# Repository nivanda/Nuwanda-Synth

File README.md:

# Nuwanda-Synth
## Chord VCO:
Original Author: HAGIWO  
Link: https://www.youtube.com/watch?v=HeWXebKo_Yk&list=PLY98KKRLWqR2VkyIqR4JTxg3VBtVM9B-y&index=44  
## Mono/Sub VCO
Original Author: HAGIWO  
Link: https://www.youtube.com/watch?v=HBtc5oQffu8&list=PLY98KKRLWqR2VkyIqR4JTxg3VBtVM9B-y&index=40

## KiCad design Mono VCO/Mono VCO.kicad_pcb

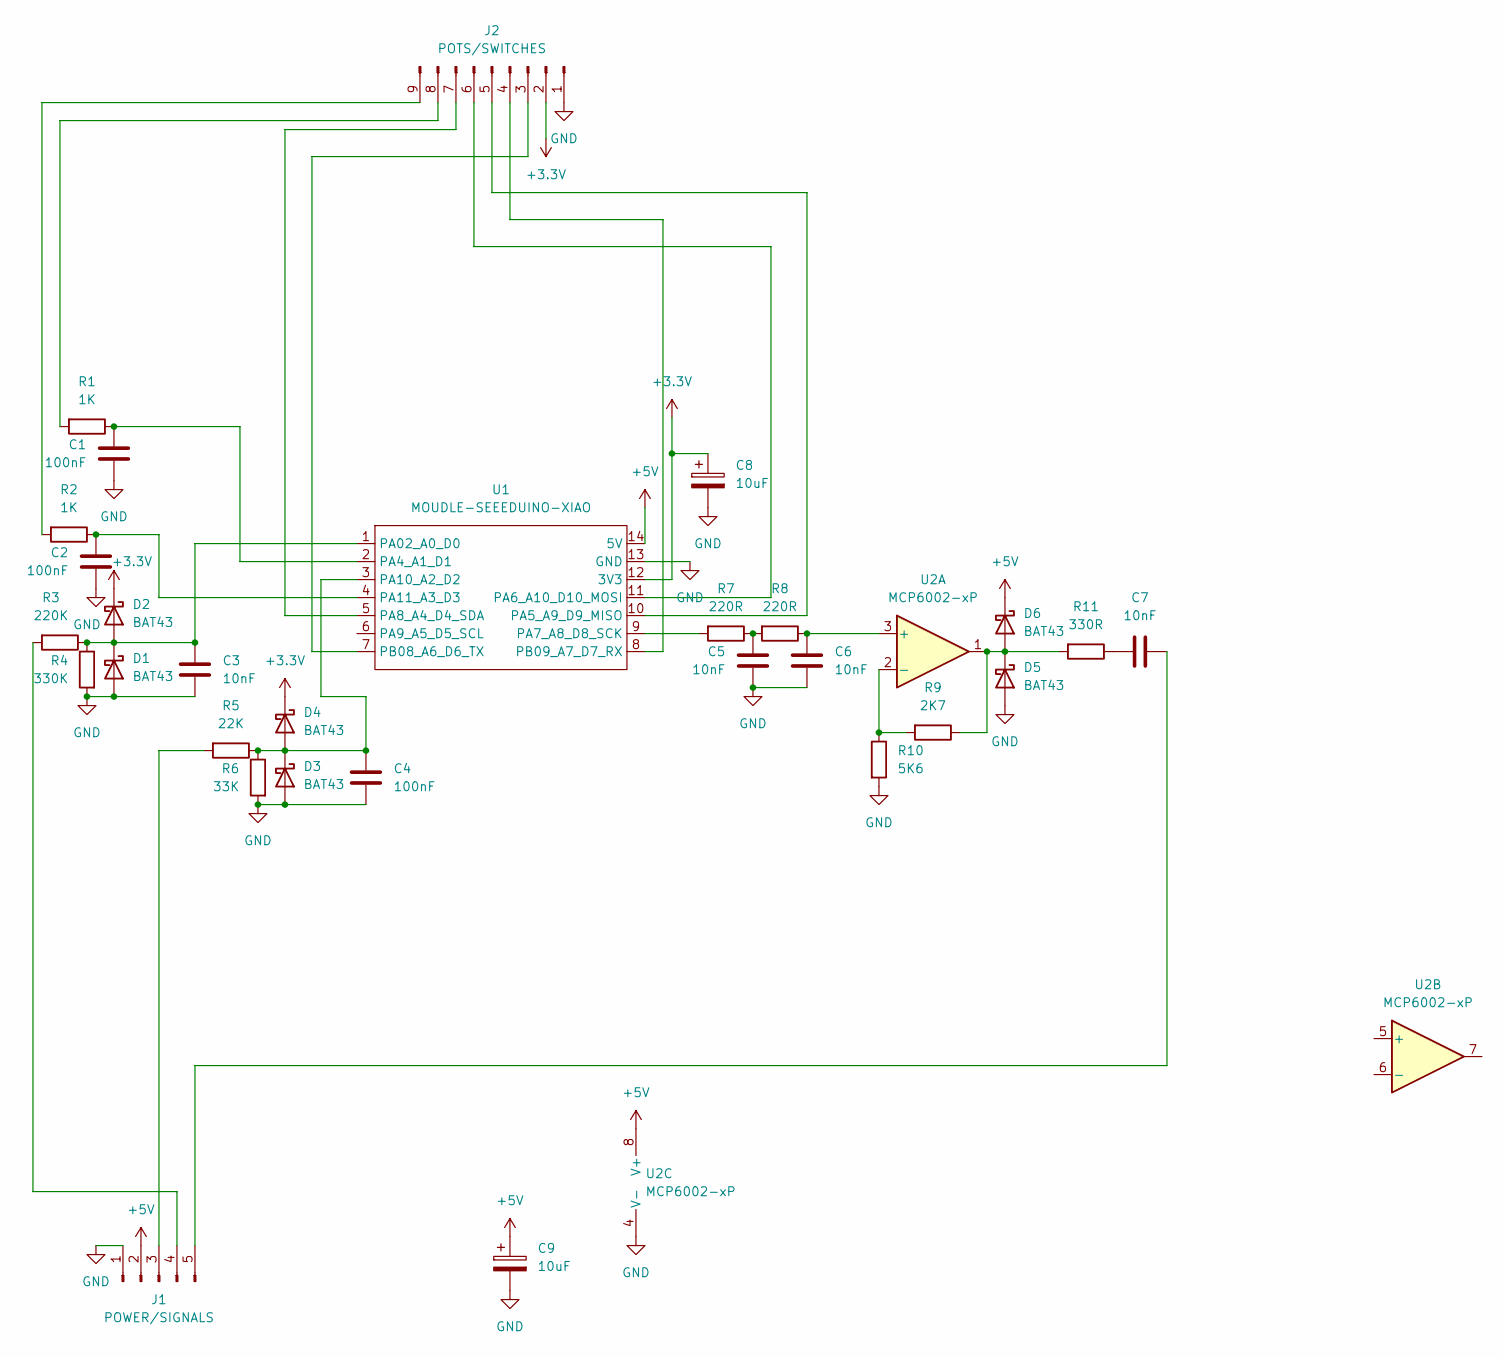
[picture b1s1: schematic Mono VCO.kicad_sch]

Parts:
C1, C2, C4: 100nF; C_Disc_D5.0mm_W2.5mm_P5.00mm
C3, C5, C6, C7: 10nF; C_Disc_D5.0mm_W2.5mm_P5.00mm
C8, C9: 10uF; CP_Radial_D5.0mm_P2.50mm
D1, D2, D3, D4, D5, D6: BAT43; D_DO-35_SOD27_P7.62mm_Horizontal
J1: POWER/SIGNALS; PinHeader_1x05_P2.54mm_Horizontal
J2: POTS/SWITCHES; PinHeader_1x09_P2.54mm_Horizontal
R1, R2: 1K; R_Axial_DIN0207_L6.3mm_D2.5mm_P10.16mm_Horizontal
R3: 220K; R_Axial_DIN0207_L6.3mm_D2.5mm_P10.16mm_Horizontal
R4: 330K; R_Axial_DIN0207_L6.3mm_D2.5mm_P10.16mm_Horizontal
R5: 22K; R_Axial_DIN0207_L6.3mm_D2.5mm_P10.16mm_Horizontal
R6: 33K; R_Axial_DIN0207_L6.3mm_D2.5mm_P10.16mm_Horizontal
R7, R8: 220R; R_Axial_DIN0207_L6.3mm_D2.5mm_P10.16mm_Horizontal
R9: 2K7; R_Axial_DIN0207_L6.3mm_D2.5mm_P10.16mm_Horizontal
R10: 5K6; R_Axial_DIN0207_L6.3mm_D2.5mm_P10.16mm_Horizontal
R11: 330R; R_Axial_DIN0207_L6.3mm_D2.5mm_P10.16mm_Horizontal
U1: MOUDLE-SEEEDUINO-XIAO; MOUDLE14P-2.54-21X17.8MM
U2: MCP6002-xP; DIP-8_W7.62mm_Socket

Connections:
+3.3V: C8.1, D2.1 (K), D4.1 (K), J2.2, U1.12 (3V3)
+5V: C9.1, D6.1 (K), J1.2, U1.14 (5V), U2.8 (V+)
GND: C1.2, C2.2, C3.2, C4.2, C5.2, C6.2, C8.2, C9.2, D1.2 (A), D3.2 (A), D5.2 (A), J1.1, J2.1, R4.2, R6.2, R10.2, U1.13 (GND), U2.4 (V-)
unnamed: C5.1, R7.1, R8.2
unnamed: C7.2, R11.1
unnamed: C3.1, D1.1 (K), D2.2 (A), R3.1, R4.1, U1.1 (PA02_A0_D0)
unnamed: C4.1, D3.1 (K), D4.2 (A), R5.1, R6.1, U1.3 (PA10_A2_D2)
unnamed: D5.1 (K), D6.2 (A), R9.1, R11.2, U2.1
unnamed: J1.3, R5.2
unnamed: J1.4, R3.2
unnamed: C7.1, J1.5
unnamed: J2.3, U1.7 (PB08_A6_D6_TX)
unnamed: J2.4, U1.8 (PB09_A7_D7_RX)
unnamed: J2.5, U1.10 (PA5_A9_D9_MISO)
unnamed: J2.6, U1.11 (PA6_A10_D10_MOSI)
unnamed: J2.7, U1.5 (PA8_A4_D4_SDA)
unnamed: J2.8, R1.2
unnamed: J2.9, R2.2
unnamed: C1.1, R1.1, U1.2 (PA4_A1_D1)
unnamed: R7.2, U1.9 (PA7_A8_D8_SCK)
unnamed: C2.1, R2.1, U1.4 (PA11_A3_D3)
unnamed: C6.1, R8.1, U2.3 (+)
unnamed: R9.2, R10.1, U2.2 (-)

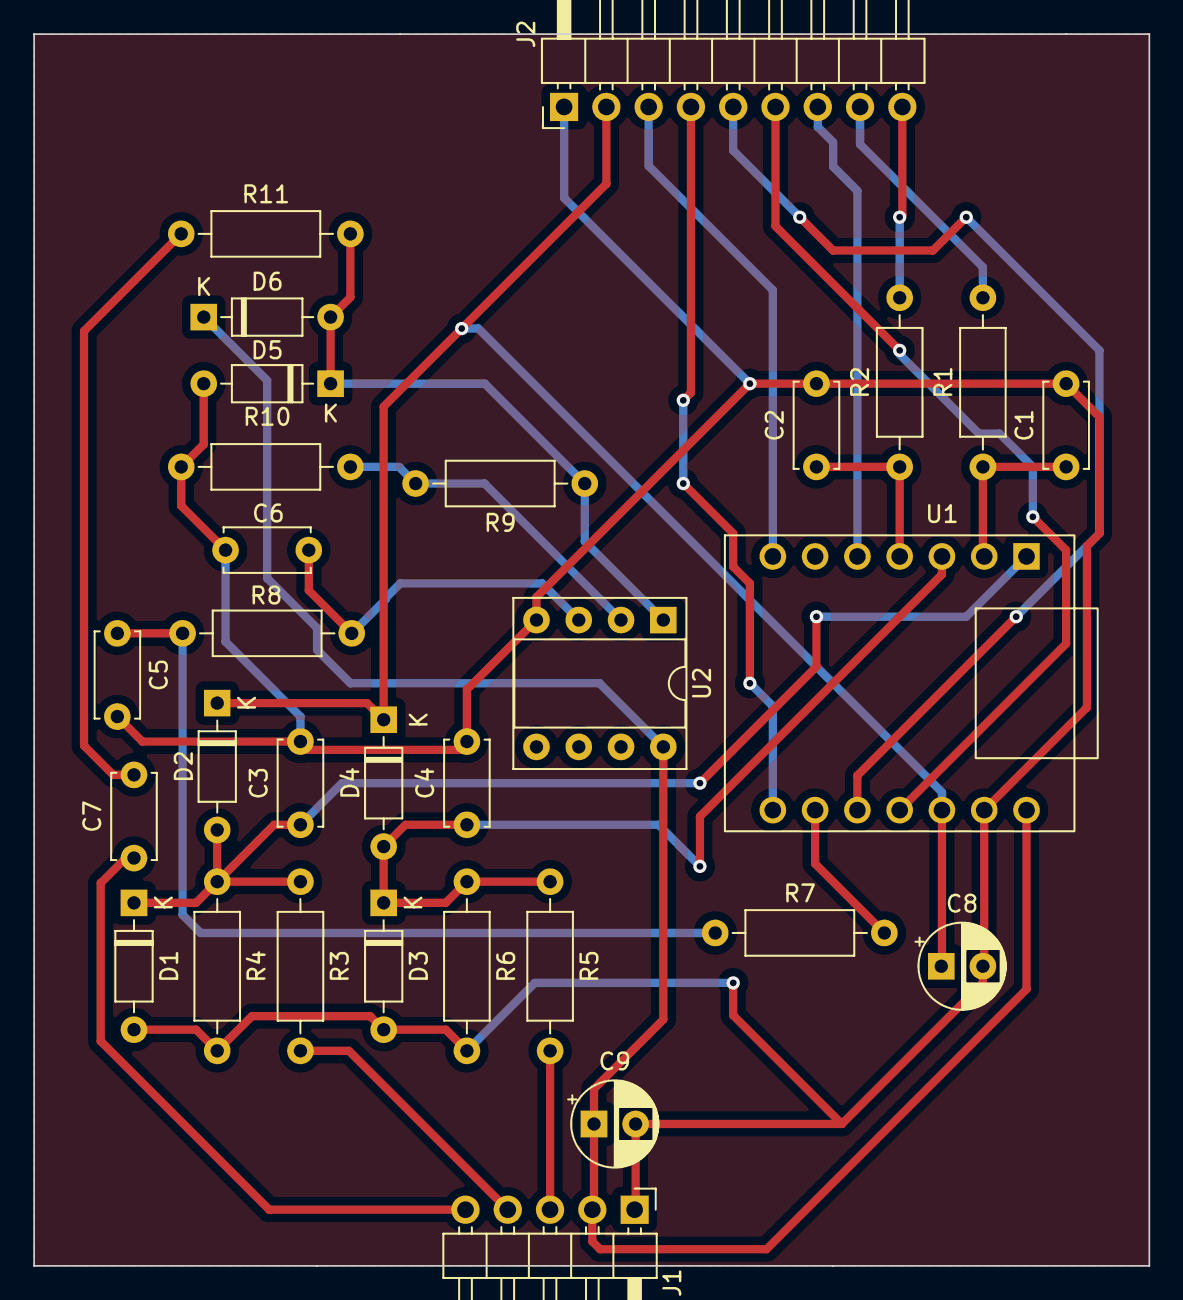
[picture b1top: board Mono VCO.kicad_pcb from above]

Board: 2 copper layers, 67.0 x 74.0 mm, 30 parts (0 on the bottom side), 23 nets.

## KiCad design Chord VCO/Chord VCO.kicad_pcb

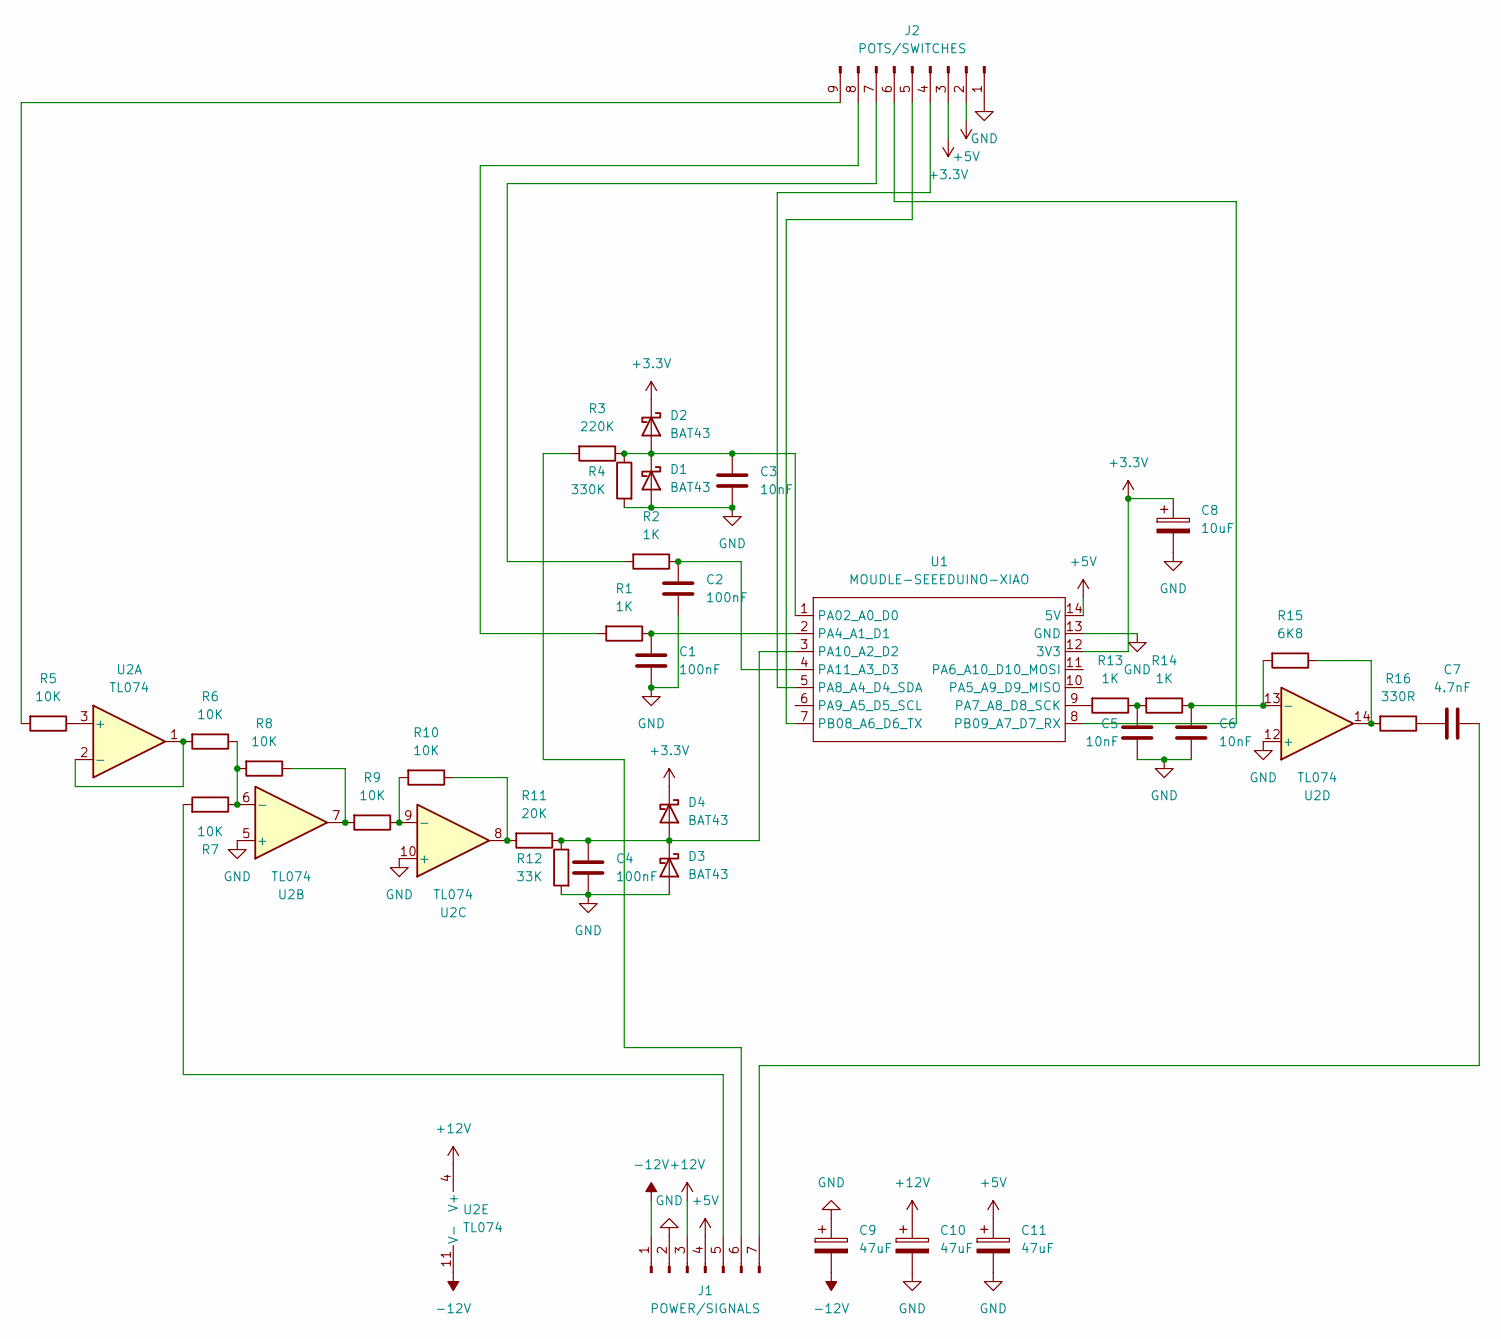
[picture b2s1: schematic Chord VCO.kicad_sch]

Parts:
C1, C2, C4: 100nF; C_Disc_D4.7mm_W2.5mm_P5.00mm
C3, C5, C6: 10nF; C_Disc_D4.7mm_W2.5mm_P5.00mm
C7: 4.7nF; C_Disc_D4.7mm_W2.5mm_P5.00mm
C8: 10uF; CP_Radial_D5.0mm_P2.50mm
C9, C10, C11: 47uF; CP_Radial_D5.0mm_P2.00mm
D1, D2, D3, D4: BAT43; D_DO-35_SOD27_P10.16mm_Horizontal
J1: POWER/SIGNALS; PinHeader_1x07_P2.54mm_Horizontal
J2: POTS/SWITCHES; PinHeader_1x09_P2.54mm_Horizontal
R1, R2, R13, R14: 1K; R_Axial_DIN0411_L9.9mm_D3.6mm_P15.24mm_Horizontal
R3: 220K; R_Axial_DIN0411_L9.9mm_D3.6mm_P15.24mm_Horizontal
R4: 330K; R_Axial_DIN0411_L9.9mm_D3.6mm_P15.24mm_Horizontal
R5, R6, R7, R8, R9, R10: 10K; R_Axial_DIN0411_L9.9mm_D3.6mm_P15.24mm_Horizontal
R11: 20K; R_Axial_DIN0411_L9.9mm_D3.6mm_P15.24mm_Horizontal
R12: 33K; R_Axial_DIN0411_L9.9mm_D3.6mm_P15.24mm_Horizontal
R15: 6K8; R_Axial_DIN0411_L9.9mm_D3.6mm_P15.24mm_Horizontal
R16: 330R; R_Axial_DIN0411_L9.9mm_D3.6mm_P15.24mm_Horizontal
U1: MOUDLE-SEEEDUINO-XIAO; MOUDLE14P-2.54-21X17.8MM
U2: TL074; DIP-14_W7.62mm_Socket

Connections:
+3.3V: C8.1, D2.1 (K), D4.1 (K), J2.3, U1.12 (3V3)
+5V: C11.1, J1.4, J2.2, U1.14 (5V)
+12V: C10.1, J1.3, U2.4 (V+)
-12V: C9.2, J1.1, U2.11 (V-)
GND: C1.2, C2.2, C3.2, C4.2, C5.2, C6.2, C8.2, C9.1, C10.2, C11.2, D1.2 (A), D3.2 (A), J1.2, J2.1, R4.2, R12.2, U1.13 (GND), U2.5 (+), U2.10 (+), U2.12 (+)
unnamed: C5.1, R13.1, R14.2
unnamed: C7.2, R16.1
unnamed: C3.1, D1.1 (K), D2.2 (A), R3.1, R4.1, U1.1 (PA02_A0_D0)
unnamed: C4.1, D3.1 (K), D4.2 (A), R11.1, R12.1, U1.3 (PA10_A2_D2)
unnamed: J1.5, R7.2
unnamed: J1.6, R3.2
unnamed: C7.1, J1.7
unnamed: J2.4, U1.5 (PA8_A4_D4_SDA)
unnamed: J2.5, U1.7 (PB08_A6_D6_TX)
unnamed: J2.6, U1.8 (PB09_A7_D7_RX)
unnamed: J2.7, R2.2
unnamed: J2.8, R1.2
unnamed: J2.9, R5.2
unnamed: R8.1, R9.2, U2.7
unnamed: R10.1, R11.2, U2.8
unnamed: R15.1, R16.2, U2.14
unnamed: C1.1, R1.1, U1.2 (PA4_A1_D1)
unnamed: R13.2, U1.9 (PA7_A8_D8_SCK)
unnamed: C2.1, R2.1, U1.4 (PA11_A3_D3)
unnamed: R5.1, U2.3 (+)
unnamed: R6.2, U2.1, U2.2 (-)
unnamed: R6.1, R7.1, R8.2, U2.6 (-)
unnamed: R9.1, R10.2, U2.9 (-)
unnamed: C6.1, R14.1, R15.2, U2.13 (-)

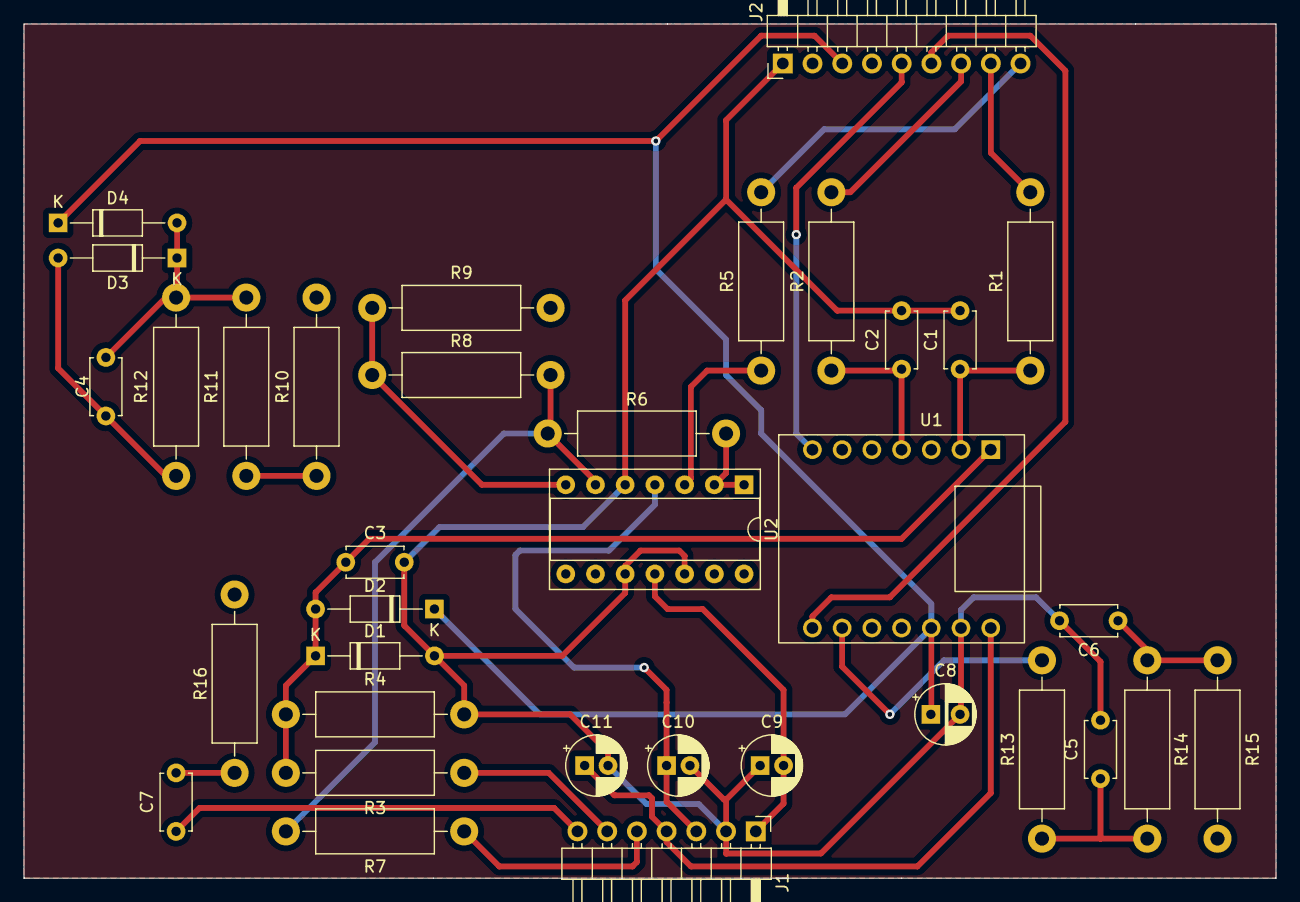
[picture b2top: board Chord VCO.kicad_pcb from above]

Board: 4 copper layers, 107.0 x 73.0 mm, 35 parts (0 on the bottom side), 29 nets.

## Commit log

2023-12-30 Added Chord VCO schematic and PCB
2023-12-30 Fixed README file
2023-12-30 Another try at fixing the README file
2023-12-30 Added fill zones to Chord VCO pcb
2023-12-30 Added Mono/Sub VCO schematic and PCB
